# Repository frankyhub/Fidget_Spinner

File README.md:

<div align="center">

|[:skull:ISSUE](https://github.com/frankyhub/Fidget_Spinner/issues?q=is%3Aissue)|[:speech_balloon: Forum /Discussion](https://github.com/frankyhub/Fidget_Spinner/discussions)|[:grey_question:WiKi](https://github.com/frankyhub/Fidget_Spinner/wiki)||
|--|--|--|--|
| | | | |
<a href="https://github.com/frankyhub/Fidget_Spinner/issues">|<a href="https://github.com/frankyhub/Fidget_Spinner/discussions">|<a href="https://github.com/frankyhub/Fidget_Spinner/6eleases">||
|| <a href="https://github.com/frankyhub/Fidget_Spinner/pulse" alt="Activity">| <a href="https://github.com/frankyhub/Fidget_Spinner/graphs/traffic">  |<a href="https://github.com/frankyhub?tab=stars"> ||

<br> <br>

</div>

## Hardware

| Anzahl | Bezeichnung | 
| -------- | -------- | 
| 3  | SMD Bat.Holder   |
| 3  |  CR2032  |
| 1  |  Mini-Schalter  |
|  1 |  1k  |
|  3 |  150R  |
| 9  |  LEDs  |
| 1  |  SW-200D  |
| 1  | BC846B   |
|  1 | Kugellager 22mm   | 
|  1 |  Platine  | 
| ---  |  ---  | 

---

<div style="position:absolute; left:2cm; ">   
<ol class="breadcrumb" style="border-top: 2px solid black;border-bottom:2px solid black; height: 45px; width: 900px;"> <p align="center"><a href="#oben">nach oben</a></p></ol>
</div>  

---

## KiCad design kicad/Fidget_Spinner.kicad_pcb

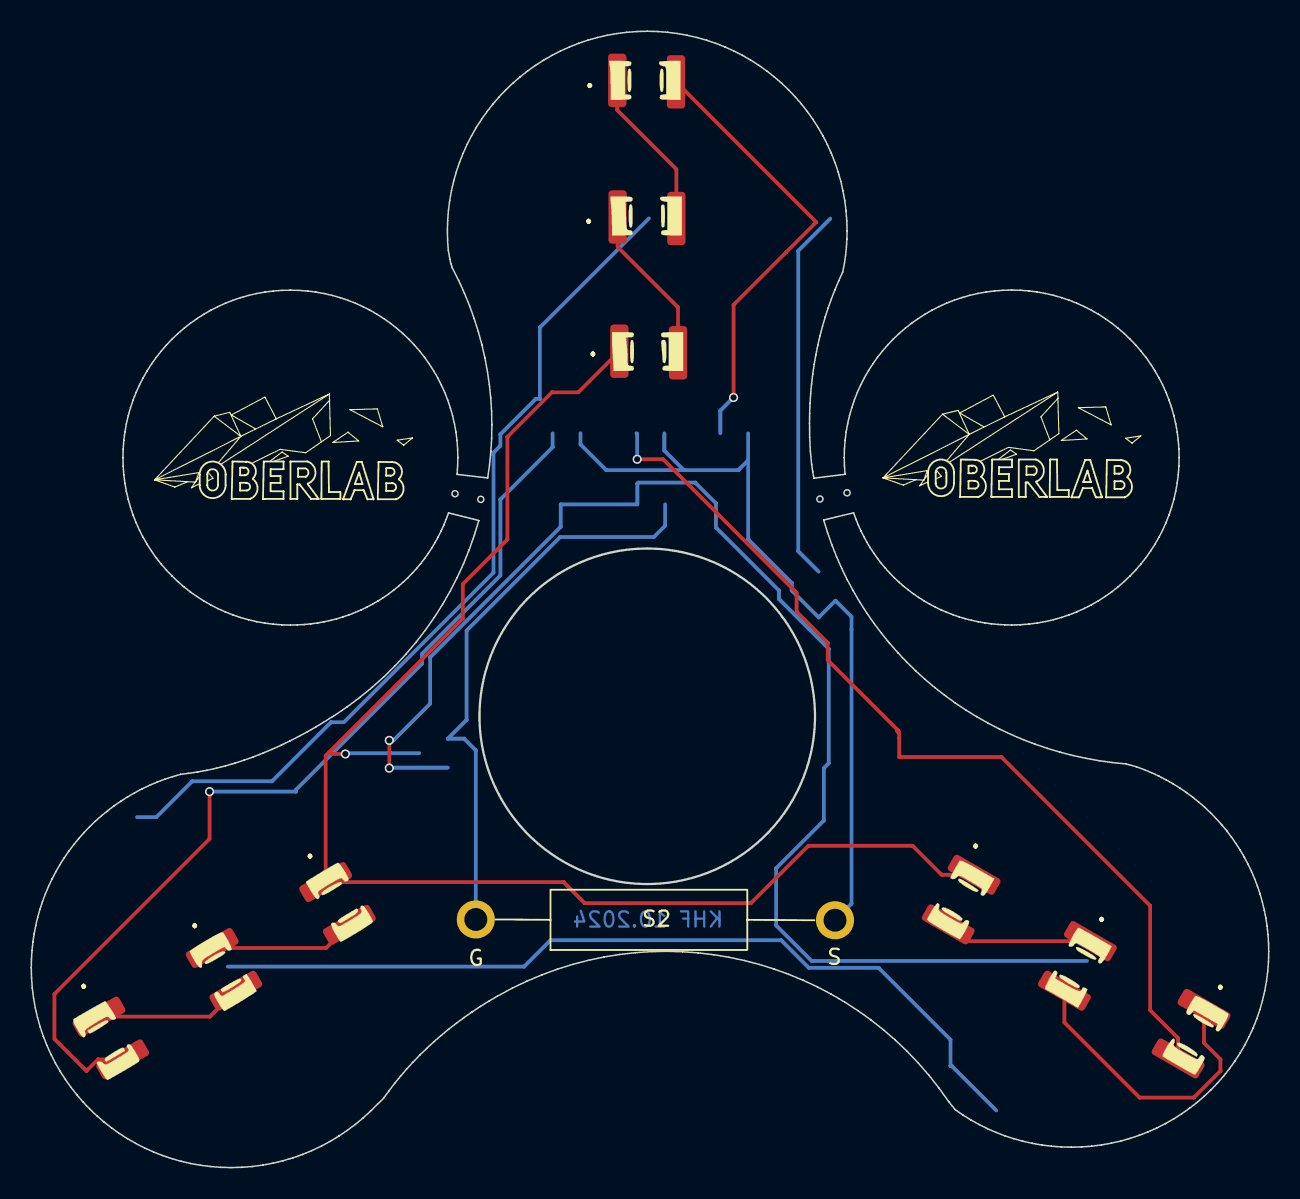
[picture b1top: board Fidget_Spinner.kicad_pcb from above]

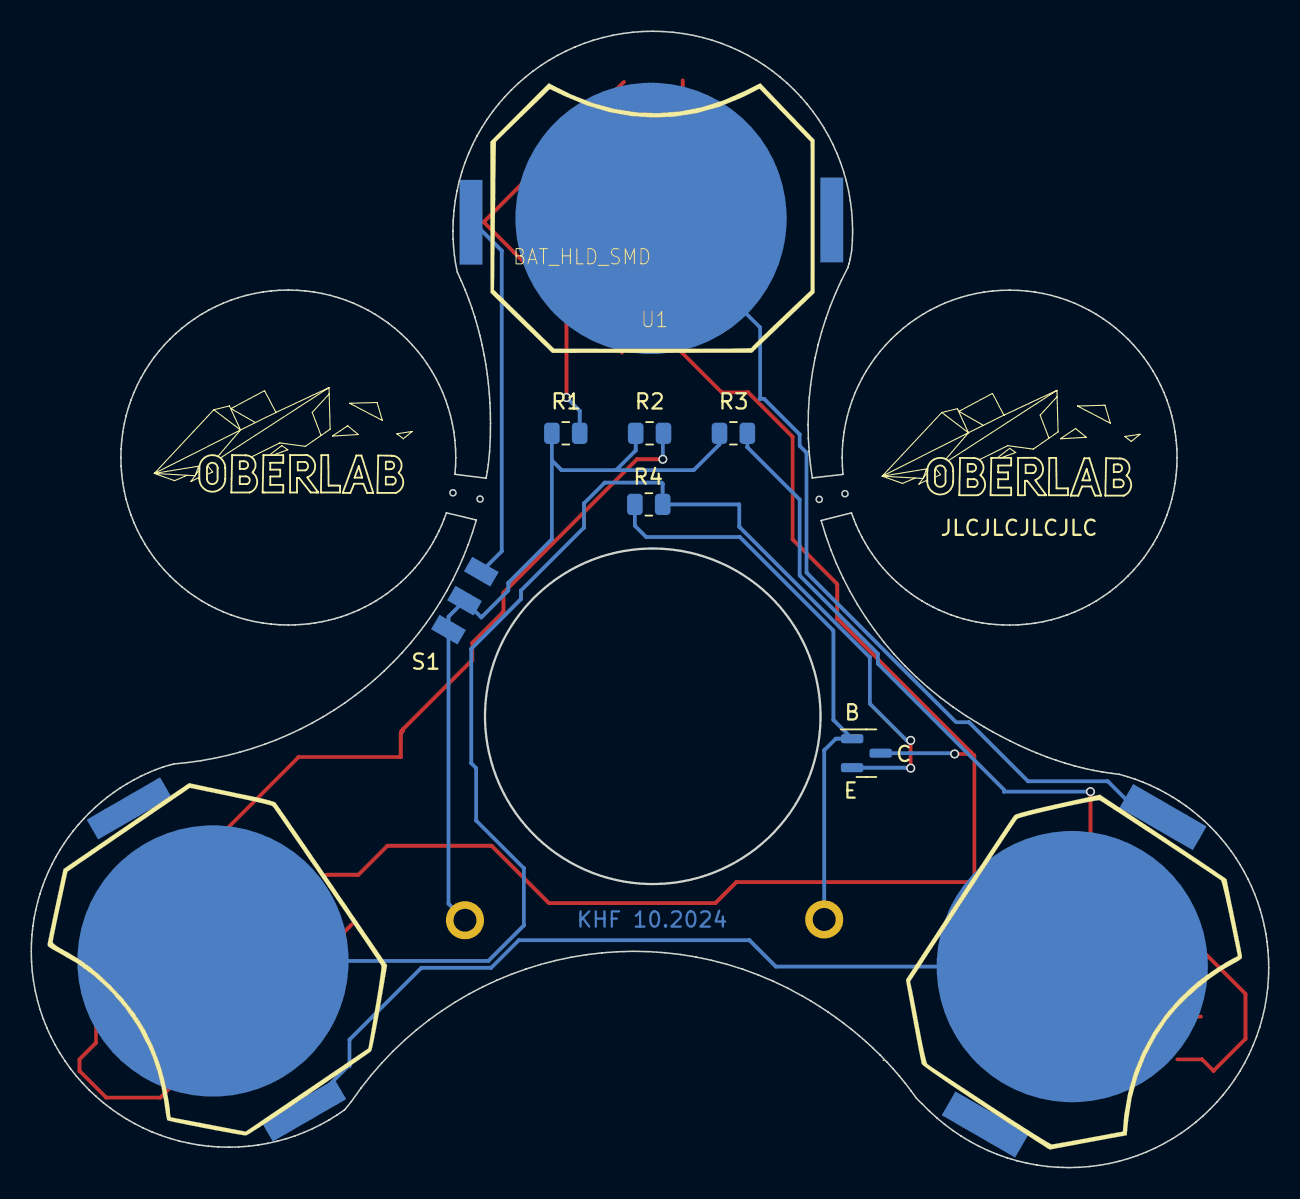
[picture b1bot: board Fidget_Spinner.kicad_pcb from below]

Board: 2 copper layers, 81.1 x 74.5 mm, 19 parts (6 on the bottom side), 15 nets.

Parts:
D1, D2, D3: LED; C_1812_4532Metric_0
D4, D5, D6: LED; C_1812_4532Metric_60
D7, D8, D9: LED; C_1812_4532Metric_300
Q1: BC846; SOT-23
R1, R2, R3, R4: R; R_0805_2012Metric
S1: Micro_Schalter; Micro_SchalterKHF_FS
S2: SW-200D
U1: BAT_HLD_SMD; BAT-HLD-SMD-Blech FS
U2: BAT_HLD_SMD; BAT-HLD-SMD-Blech FS_60
U3: BAT_HLD_SMD; BAT-HLD-SMD-Blech FS_300

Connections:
unnamed: D1.2 (A), R1.2
unnamed: D1.1 (K), D2.2 (A)
unnamed: D2.1 (K), D3.2 (A)
unnamed: D3.1 (K), D6.1 (K), D9.1 (K), Q1.3 (C)
unnamed: D4.2 (A), R2.2
unnamed: D4.1 (K), D5.2 (A)
unnamed: D5.1 (K), D6.2 (A)
unnamed: D7.2 (A), R3.2
unnamed: D7.1 (K), D8.2 (A)
unnamed: D8.1 (K), D9.2 (A)
unnamed: Q1.1 (B), R4.1, S2.2 (Gold)
unnamed: Q1.2 (E), R4.2, U2.2
unnamed: S1.1 (A), U1.1
unnamed: R1.1, R2.1, R3.1, S1.2 (E), S1.3 (A), S2.1 (Silber)
unnamed: U1.2, U3.1

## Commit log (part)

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2024-08-08 V 08082024
2024-08-10 V 10082024
2024-08-19 V 19.08.2024
2024-08-22 V 22.08.2024
2024-09-01 V 01092024
2024-09-10 V 10092024
2024-10-04 V 04102024
2024-10-12 V12102024
